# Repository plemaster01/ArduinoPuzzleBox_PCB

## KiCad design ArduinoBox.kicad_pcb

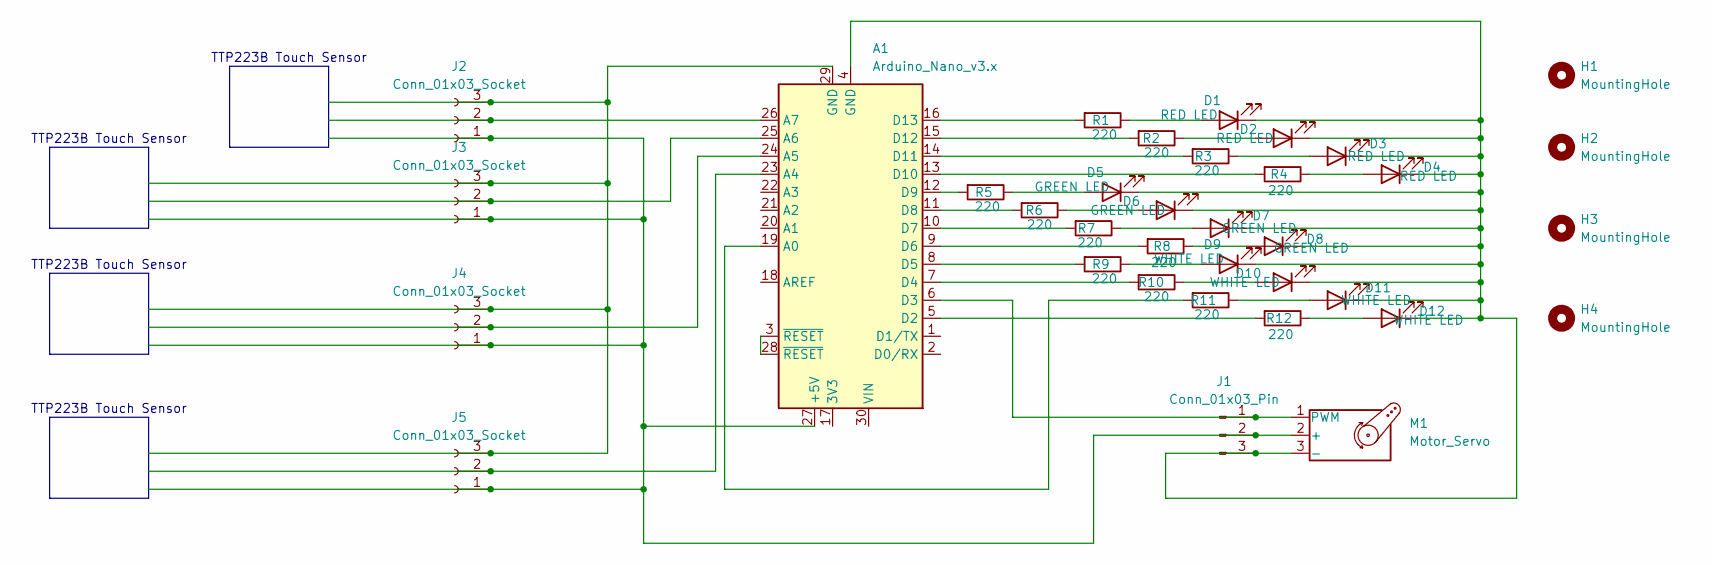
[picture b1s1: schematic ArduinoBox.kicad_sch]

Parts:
A1: Arduino_Nano_v3.x; Arduino_Nano
D1, D2, D3, D4: RED LED; LED_D3.0mm
D5, D6, D7, D8: GREEN LED; LED_D3.0mm
D9, D10, D11, D12: WHITE LED; LED_D3.0mm
H1, H2, H3, H4: MountingHole; MountingHole_3.2mm_M3
J1: Conn_01x03_Pin; PinHeader_1x03_P2.54mm_Horizontal
J2, J3, J4, J5: Conn_01x03_Socket; PinSocket_1x03_P2.54mm_Horizontal
M1: Motor_Servo
R1, R2, R3, R4, R5, R6, R7, R8, R9, R10, R11, R12: 220; R_Axial_DIN0204_L3.6mm_D1.6mm_P5.08mm_Horizontal

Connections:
unnamed: A1.27 (+5V), J1.2, J2.1, J3.1, J4.1, J5.1, M1.2 (+)
unnamed: A1.19 (A0), R11.2
unnamed: A1.23 (A4), J5.2
unnamed: A1.24 (A5), J4.2
unnamed: A1.25 (A6), J3.2
unnamed: A1.26 (A7), J2.2
unnamed: A1.5 (D2), R12.2
unnamed: A1.6 (D3), J1.1, M1.1 (PWM)
unnamed: A1.7 (D4), R10.2
unnamed: A1.8 (D5), R9.2
unnamed: A1.9 (D6), R8.2
unnamed: A1.10 (D7), R7.2
unnamed: A1.11 (D8), R6.2
unnamed: A1.12 (D9), R5.2
unnamed: A1.13 (D10), R4.2
unnamed: A1.14 (D11), R3.2
unnamed: A1.15 (D12), R2.2
unnamed: A1.16 (D13), R1.2
unnamed: A1.3 (~RESET), A1.28 (~RESET)
unnamed: D1.2 (A), R1.1
unnamed: A1.4 (GND), D1.1 (K), D2.1 (K), D3.1 (K), D4.1 (K), D5.1 (K), D6.1 (K), D7.1 (K), D8.1 (K), D9.1 (K), D10.1 (K), D11.1 (K), D12.1 (K), J1.3, M1.3 (-)
unnamed: D2.2 (A), R2.1
unnamed: D3.2 (A), R3.1
unnamed: D4.2 (A), R4.1
unnamed: D5.2 (A), R5.1
unnamed: D6.2 (A), R6.1
unnamed: D7.2 (A), R7.1
unnamed: D8.2 (A), R8.1
unnamed: D9.2 (A), R9.1
unnamed: D10.2 (A), R10.1
unnamed: D11.2 (A), R11.1
unnamed: D12.2 (A), R12.1
unnamed: A1.29 (GND), J2.3, J3.3, J4.3, J5.3

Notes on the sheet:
TTP223B Touch Sensor

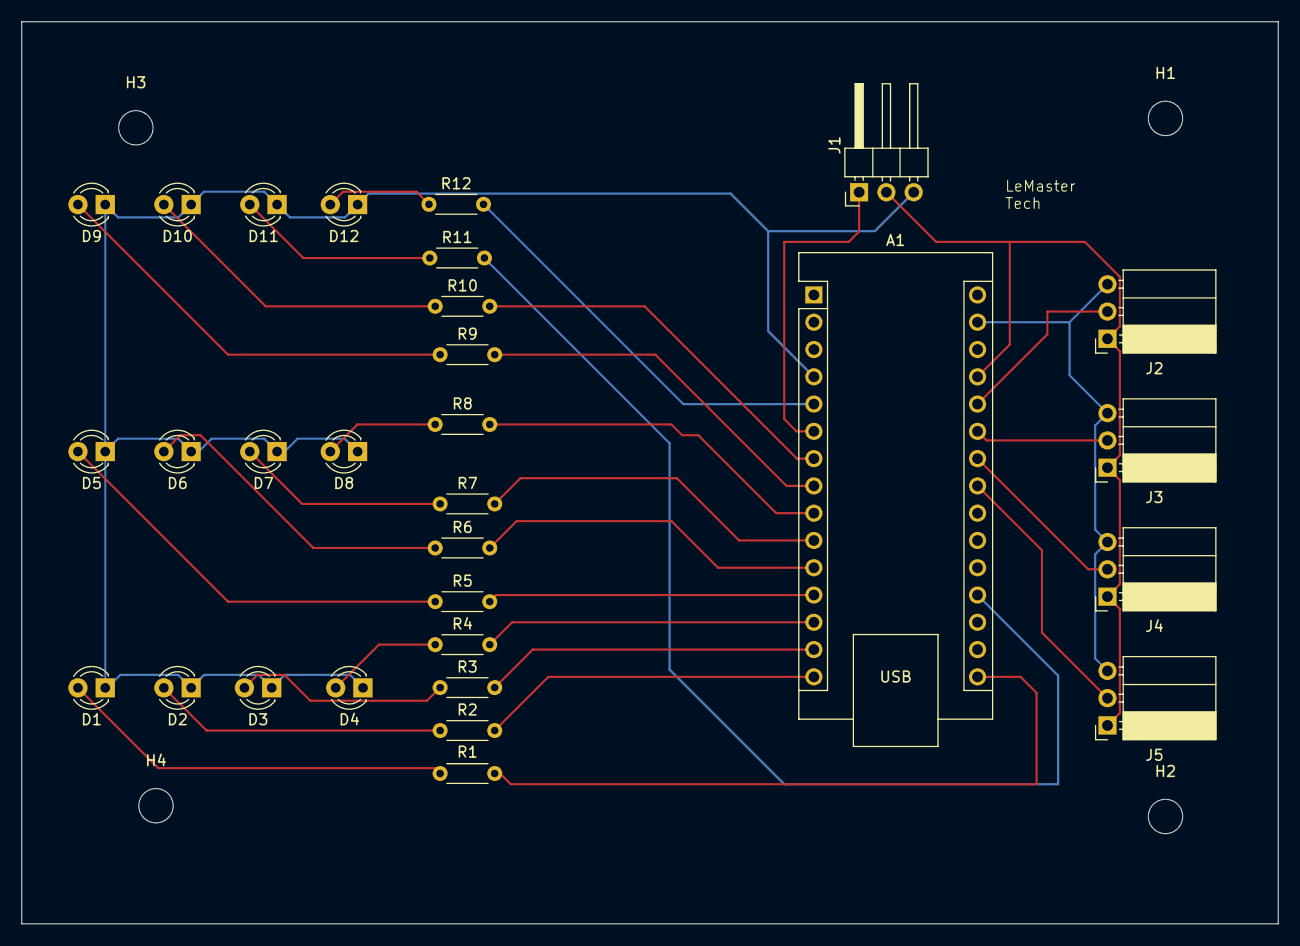
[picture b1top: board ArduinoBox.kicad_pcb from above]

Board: 2 copper layers, 117.0 x 84.0 mm, 34 parts (0 on the bottom side), 33 nets.
